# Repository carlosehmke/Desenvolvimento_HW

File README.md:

# Projetos de Desenvolvimento de Hardware Eletrônico ⚡

Este repositório é destinado ao armazenamento e organização de **projetos de hardware eletrônico**.  
O objetivo é reunir esquemáticos, PCBs, simulações, códigos auxiliares e documentação técnica relacionados a circuitos analógicos, digitais e de instrumentação.

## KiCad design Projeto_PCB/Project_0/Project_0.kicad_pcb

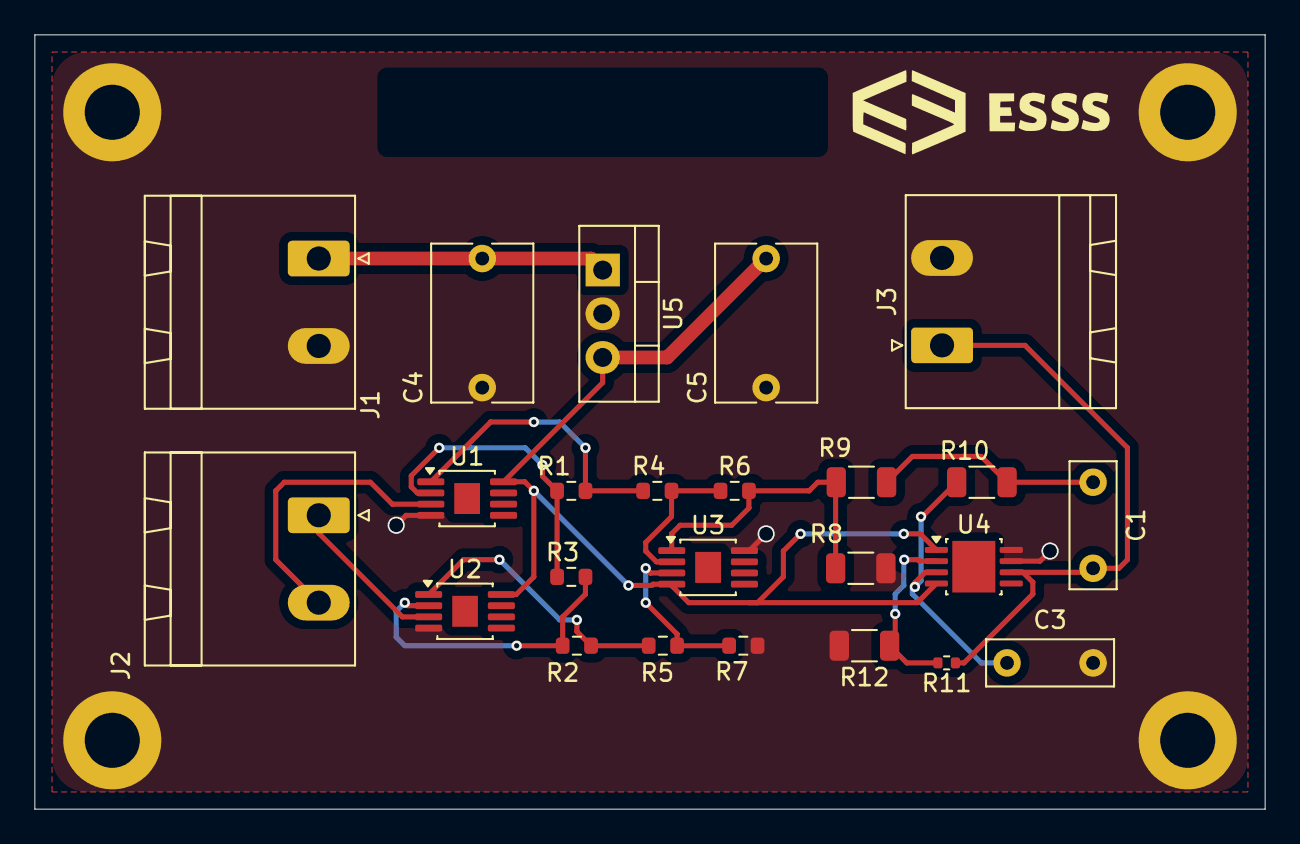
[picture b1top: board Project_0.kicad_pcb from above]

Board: 2 copper layers, 71.5 x 45.0 mm, 24 parts (0 on the bottom side), 16 nets.

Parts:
C1, C3: 1uF; C_Rect_L7.2mm_W2.5mm_P5.00mm_FKS2_FKP2_MKS2_MKP2
C4, C5: 0.1uF; C_Rect_L9.0mm_W5.7mm_P7.50mm_MKT
J1, J2, J3: Conn_01x02; PhoenixContact_MSTBA_2,5_2-G-5,08_1x02_P5.08mm_Horizontal
R1, R2, R4, R5, R6, R7: 1k; R_0603_1608Metric
R3: 75; R_0603_1608Metric
R8: 1k; R_1206_3216Metric
R9, R10: 158k; R_1206_3216Metric
R11: 100k; R_0402_1005Metric
R12: 59k; R_1206_3216Metric
U1, U2, U3: ADA4522-1; MSOP-8-1EP_3x3mm_P0.65mm_EP1.5x1.8mm
U4: LTC2057; MSOP-8-1EP_3x3mm_P0.65mm_EP2.5x3mm_Mask1.73x2.36mm
U5: LM7805_TO220; TO-220-3_Vertical

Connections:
/Amp_out: R6.2, R8.2, R9.2, U3.1
/Final_out: C1.2, J3.1, R11.1, U4.6
/Voltage_regulator/V_bat: C4.1, J1.1, U5.1 (VI)
/Vt+: J2.1, U2.3 (+)
/Vt-: J2.2, U1.3 (+)
GND: C3.2, C4.2, C5.2, J1.2, J3.2, R7.1, R8.1, R12.2, U1.4 (V-), U2.4 (V-), U3.8 (V+), U4.7 (V-), U4.8 (SDCOM), U5.2 (GND)
unnamed: C1.1, R9.1, R10.2
unnamed: R1.2, R4.1, U1.1
unnamed: R2.2, R5.1, U2.1
unnamed: R1.1, R3.1, U1.2 (-)
unnamed: R2.1, R3.2, U2.2 (-)
unnamed: R5.2, R7.2, U3.3 (+)
unnamed: R4.2, R6.1, U3.2 (-)
unnamed: C3.1, R10.1, U4.3 (+)
unnamed: R11.2, R12.1, U4.2 (-)
VCC: C5.1, U1.8 (V+), U2.8 (V+), U3.4 (V-), U4.1 (SD), U4.4 (V+), U5.3 (VO)

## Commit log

2025-10-14 Organizando Pastas
2025-10-14 Organizando e deletando pastas
2025-10-14 Cirando README file
2025-10-14 Alterando readme do projeto 0
2025-10-23 Adicionando Projeto_1
2025-10-23 Criando pasta PCB
